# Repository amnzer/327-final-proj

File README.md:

# Beat Saber

## Overview

For our ELEC 327 final project, we tried to recreate the game [Beat Saber](https://www.beatsaber.com/) on a setup involving an MSPM0G3507 microcontroller along with various other hardware like an [LED array](https://www.amazon.com/HJHX-Programmable-Individually-Addressable-Raspberry/dp/B0B771455N), [accelerometers](https://www.st.com/en/mems-and-sensors/lsm303agr.html), [a soundboard](https://www.adafruit.com/product/2220), and custom 3D-printed joysticks.

## Repo Structure

What each of the folders in this repo are for:

- game-code: Contains code for a demo version of the game which can be played in a laptop's terminal.
- microcontroller-code: Contains all of the files in the CCStudio project we made to program our microcontrollers.
- oszs: Contains content from the rhythm game osu, from which we derived the playable charts in our game.
- pcb-code: Contains KiCAD files for the PCB we made.
- website: Contains source code for the website.

## Demo

[Here's what the game looks like](https://youtube.com/shorts/_W2wUD-qPj0?feature=share)

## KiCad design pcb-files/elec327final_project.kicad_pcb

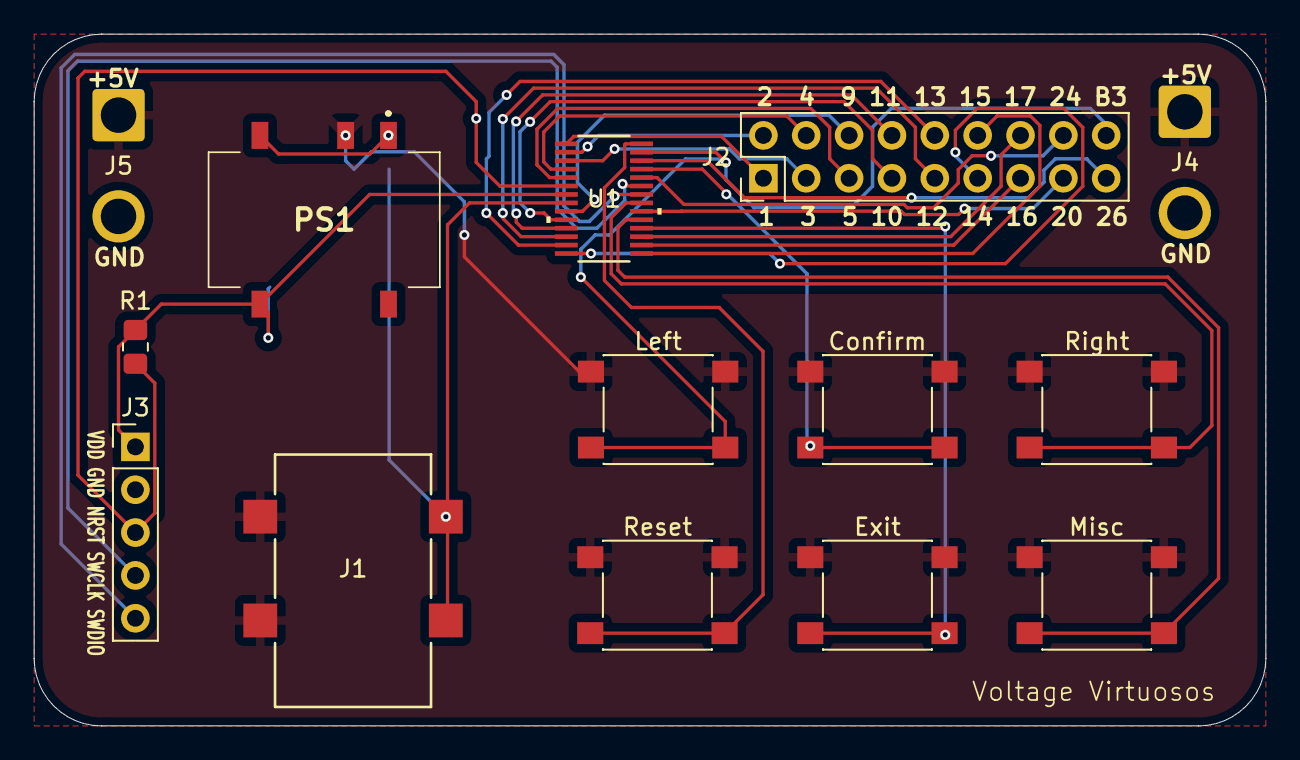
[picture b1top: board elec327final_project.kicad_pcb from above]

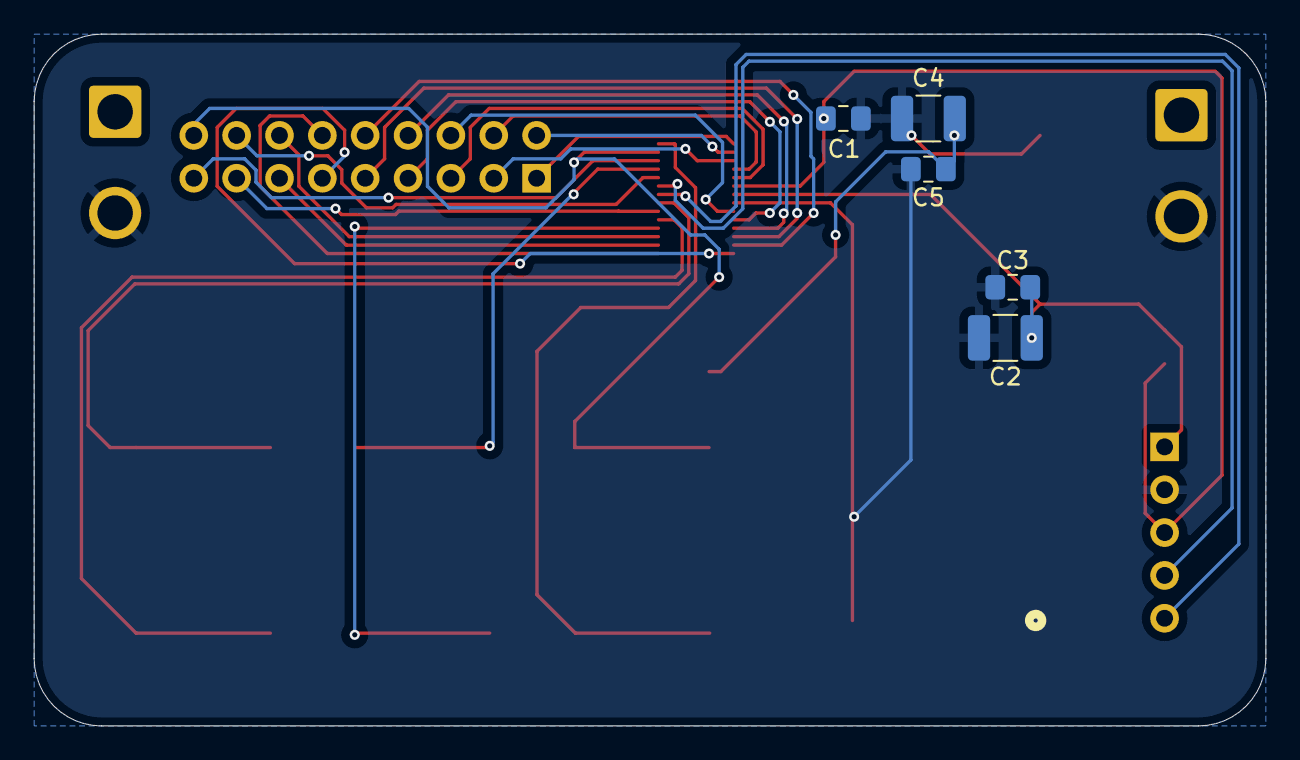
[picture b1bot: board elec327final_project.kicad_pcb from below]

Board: 2 copper layers, 73.0 x 41.0 mm, 19 parts (5 on the bottom side), 29 nets.

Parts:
C1: 10 nF; C_0805_2012Metric_Pad1.18x1.45mm_HandSolder
C2, C4: 10 uF; C_1210_3225Metric_Pad1.33x2.70mm_HandSolder
C3, C5: 0.1 uF; C_0805_2012Metric_Pad1.18x1.45mm_HandSolder
Confirm: SW_DPST; SW_SPST_PTS645
Exit: SW_DPST; SW_SPST_PTS645
J1: ADC-028-1-T/R-PA10T; ADC-028-x-T&slash_R-PA10T_ADM
J2: Conn_02x09_Counter_Clockwise; PinHeader_2x09_P2.54mm_Vertical
J3: Conn_01x05; PinHeader_1x05_P2.54mm_Vertical
J4, J5: Conn_01x02_Socket; SolderWire-1.5sqmm_1x02_P6mm_D1.7mm_OD3mm
Left: SW_DPST; SW_SPST_PTS645
Misc: SW_DPST; SW_SPST_PTS645
PS1: TES_1-0510; TES10510
R1: 47k; R_0805_2012Metric_Pad1.20x1.40mm_HandSolder
Reset: SW_DPST; SW_SPST_PTS645
Right: SW_DPST; SW_SPST_PTS645
U1: MSPM0G3507SDGS28R; VSSOP28_DGS_TEX

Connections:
BTN1: Right.2, U1.21 (PA18/A1_3)
BTN2: Confirm.2, U1.25 (PA22/CLK_OUT/A0_7)
BTN3: J2.18, Left.2, U1.27 (PA24/A0_3)
BTN4: Reset.2, U1.28 (PA25/A0_2)
BTN5: Exit.2, U1.18 (PA15/A1_0)
BTN6: Misc.2, U1.19 (PA16/A1_1/FCC_IN)
GND: C1.1, C2.2, C3.2, C4.2, C5.2, J1.2, J1.3, J3.2, J4.2, J5.2, PS1.1 (-VIN_(GND)), PS1.4 (-VOUT), U1.8 (VSS)
NRST: C1.2, J3.3, R1.2, U1.6 (NRST)
PIN1: J2.1, U1.1 (PA26/A0_1)
PIN2: J2.2, U1.2 (PA27/RTC_OUT/A0_0)
PIN3: J2.3, U1.3 (VCORE)
PIN4: J2.4, U1.4 (PA0)
PIN5: J2.5, U1.5 (PA1)
PIN9: J2.6, U1.9 (PA2/ROSC)
PIN10: J2.7, U1.10 (PA3/LFXIN)
PIN11: J2.8, U1.11 (PA4/LFCLK_IN/LFXOUT)
PIN12: J2.9, U1.12 (PA5/HFXIN/FCC_IN)
PIN13: J2.10, U1.13 (PA6/HFCLK_IN/HFXOUT)
PIN14: J2.11, U1.14 (PA9/RTC_OUT/CLK_OUT)
PIN15: J2.12, U1.15 (PA10/CLK_OUT)
PIN16: J2.13, U1.16 (PA11)
PIN17: J2.14, U1.17 (PA14/CLK_OUT/A0_12)
PIN20: J2.15, U1.20 (PA17/A1_2)
PIN24: J2.16, U1.24 (PA21/A1_7/VREF-)
PIN26: J2.17, U1.26 (PA23/VREF+)
SWCLK: J3.4, U1.23 (PA20/SWCLK)
SWDIO: J3.5, U1.22 (PA19/SWDIO)
VCC: C4.1, C5.1, Confirm.1, Exit.1, J1.1A, J1.1B, J4.1, J5.1, Left.1, Misc.1, PS1.2 (+VIN_(VCC)), Reset.1, Right.1
VDD: C2.1, C3.1, J3.1, PS1.5 (+VOUT), R1.1, U1.7 (VDD)

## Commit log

2025-04-22 readme
2025-04-22 Readme draft for game
2025-04-23 Helper functions for WS2812b interfacing
2025-04-24 osu parsing
2025-04-24 Can read osu hit objects
2025-04-24 Refactoring + thinking about reading taiko
2025-04-25 starting on code
2025-04-25 Wrote the game loading screen
2025-04-25 Progressing on the game
2025-04-25 Implementing selection carousel
2025-04-25 2/5 parts done for game
2025-04-26 Designed new way to encode hit objects
2025-04-26 Cleaning up repo
2025-04-26 Readme edits
2025-04-26 Updated int representation of notes
2025-04-26 Got C-style int representation of songs
2025-04-26 Can keep track of song time
2025-04-26 No more seg faults
2025-04-26 just solved a sneeaky ass bug
2025-04-26 Working on real-time display
2025-04-26 After great difficulty the grid does work. Now just hittracking & im good
2025-04-27 play the game in actual terminal, not vscode
2025-04-27 about to start debug
2025-04-27 Entire game rough draft in place now basically. Now just debug
2025-04-27 looking into synchronization problems
2025-04-27 timekeeping is completely cooked. looking into it
2025-04-28 Fixing timing
2025-04-28 Approaching the end
2025-04-28 Game is kinda playable
2025-04-28 Rough draft done
2025-04-30 thinking abt website
2025-04-30 website
2025-04-30 Checkpoint before theme import
2025-04-30 setup astro, can run templates on localhost
2025-05-01 New songs
2025-05-01 Directories are relative + charts are public
2025-05-01 realtime feedback. timing might be a lil cooked but w/e
2025-05-01 realtime feedback. timing might still be cooked tho
2025-05-01 Normalize audio volumes
2025-05-01 visibility
2025-05-04 About to start working on 2 channel gameplay
2025-05-04 About to modify game code
2025-05-04 Two channel gameplay draft complete
2025-05-07 minor edits + renamed repo
2025-05-07 Added PCB files and MSP code
2025-05-07 Wrote readme
2025-05-07 Touching up readme
2025-05-07 Remove notes
2025-05-07 Very minor readme edits
2025-05-08 wrote all html for website
2025-05-08 Removing sharp from ignored dependencies for vercel
2025-05-08 added sharp
2025-05-09 tailwind setup
2025-05-09 padding/margin done
2025-05-09 Website is now mediocre instead of bad
2025-05-09 website is tolerable
2025-05-13 caught some tiny typos
